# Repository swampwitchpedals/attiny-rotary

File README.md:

# ATTiny Rotary

This is an open-source project designed to fill a need that
has been missed in small-scale pedal building: a reliable rotary.

## Why
The traditional rotary is huge, has a ton of solder points, 
has a limited lifespan, and is generally awkward on a PCB. This solution
aims to use the Vimex position sensor, which has the same footprint
as a standard 16mm potentiometer, in conjunction with an ATtiny and
some CD4051 switches to make an easy [1-N]p8t rotary module.

## What
PCBs are all available in the `kicad/` directory. Arduino sketches for each
sized position-sensor (5, 6 and 8) are available in the `arduino/` directory.

*Module* refers to the PCB (`kicad/rotary-multiplexor/`) and to the completed unit with parts soldered.
*Programming Shield* refers to the Atmega shield provided in the `kicad/arduino-mega-progamming-shield/` directory.

## How
1. Solder your Attiny to the Module. 
2. Solder the power regulator and filter caps onto the Module.
3. Plug the Module in the Programming Shield.
4. Program the Atmega with the ArduinoAsISP sketch.
5. Select the Attiny board of your choice, clock speed, and set the programmer to ArduinoAsISP (NOT Arduino As ISP).
6. Select your position-sensor-size sketch and program the Attiny using the "Upload via programmer" option.
7. Attach Module to your effect PCB, with the mux-select lines (pins 7, 6 and 5) tied to each 4051 you wish to control, and the position sensor pins 3 and 2 wired to pins 2 and 3 of the Module.

## License
**DISCLAIMER**
All files and documents are provided as-is. I cannot afford to support 
questions on PCB manufacturing, assembly, or Arduino programming. There
are lots of resources out there to answer these questions.

Copyright 2023 Swamp Witch Pedals

Permission is hereby granted, free of charge, to any person obtaining a copy of this software and associated documentation files (the “Software”), to deal in the Software without restriction, including without limitation the rights to use, copy, modify, merge, publish, distribute, sublicense, and/or sell copies of the Software, and to permit persons to whom the Software is furnished to do so, subject to the following conditions:

The above copyright notice and this permission notice shall be included in all copies or substantial portions of the Software.

THE SOFTWARE IS PROVIDED “AS IS”, WITHOUT WARRANTY OF ANY KIND, EXPRESS OR IMPLIED, INCLUDING BUT NOT LIMITED TO THE WARRANTIES OF MERCHANTABILITY, FITNESS FOR A PARTICULAR PURPOSE AND NONINFRINGEMENT. IN NO EVENT SHALL THE AUTHORS OR COPYRIGHT HOLDERS BE LIABLE FOR ANY CLAIM, DAMAGES OR OTHER LIABILITY, WHETHER IN AN ACTION OF CONTRACT, TORT OR OTHERWISE, ARISING FROM, OUT OF OR IN CONNECTION WITH THE SOFTWARE OR THE USE OR OTHER DEALINGS IN THE SOFTWARE

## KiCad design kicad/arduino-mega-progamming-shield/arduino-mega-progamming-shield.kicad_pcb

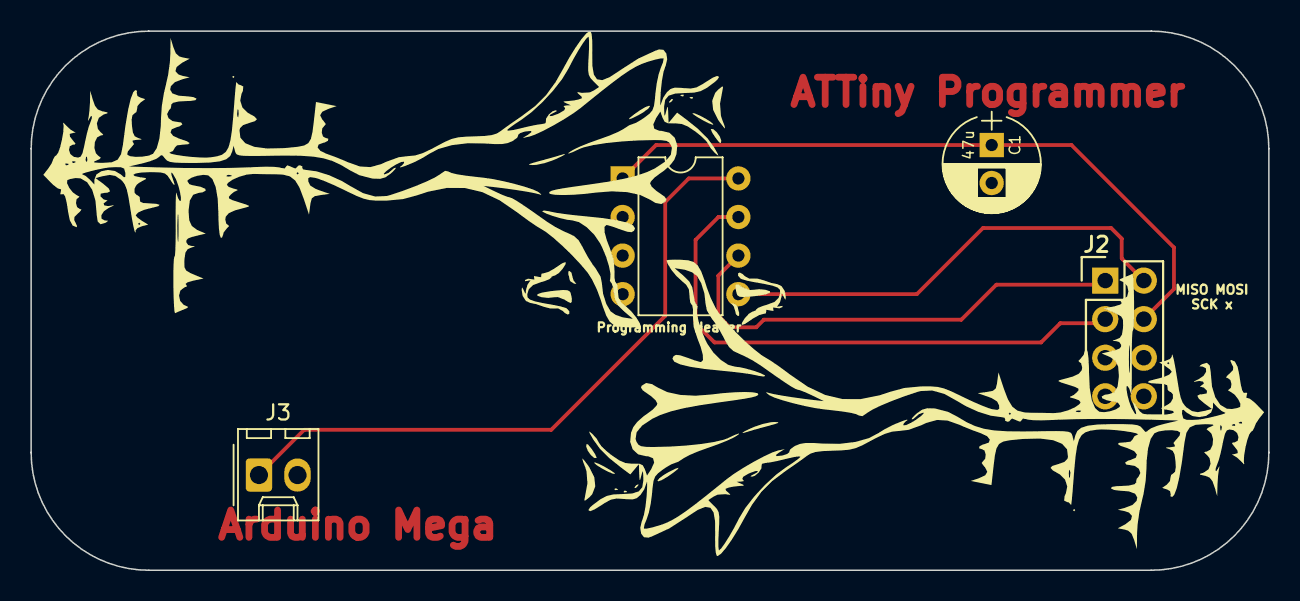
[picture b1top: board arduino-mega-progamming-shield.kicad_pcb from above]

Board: 2 copper layers, 81.5 x 35.5 mm, 4 parts (0 on the bottom side), 6 nets.

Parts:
C1: 47u; Cap_Electrolytic_TH
J1: Programming Header; DIP_8pin_TH
J2: MISO MOSI SCK x; Pin_Header_Straight_2x04
J3: Conn_01x02; Molex_KK-254_AE-6410-02A_1x02_P2.54mm_Vertical

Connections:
/+5V: J1.8, J3.1
/MISO: J1.6, J2.1
/MOSI: J1.5, J2.2
/Reset: C1.1 (+), J1.1, J2.4
/SCK: J1.7, J2.3
GND: C1.2 (-), J1.4, J3.2

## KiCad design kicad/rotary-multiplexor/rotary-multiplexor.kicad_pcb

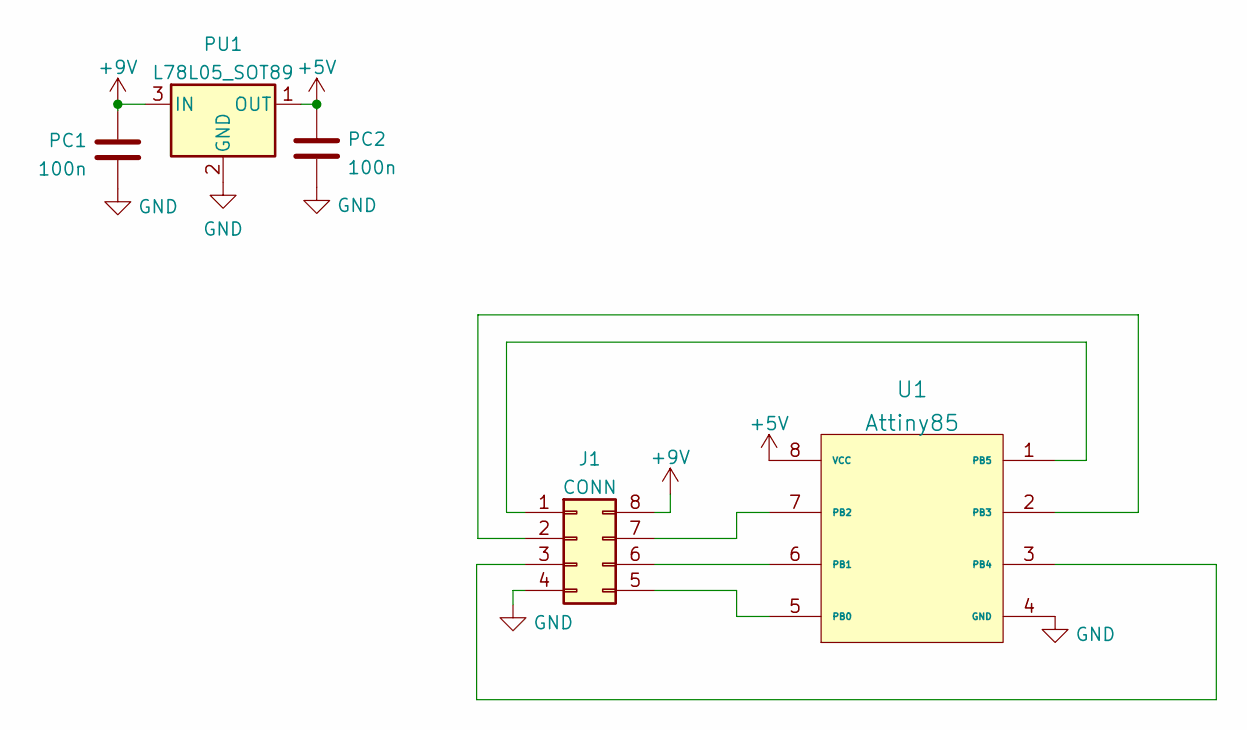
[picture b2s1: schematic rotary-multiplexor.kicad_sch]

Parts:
J1: CONN; DIP_8pin_TH
PC1, PC2: 100n; C_0805
PU1: L78L05_SOT89; SOT-89-3
U1: Attiny85; SOIC-8_3.9x4.9mm_P1.27mm

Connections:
+5V: PC2.1, PU1.1 (OUT), U1.8 (VCC)
+9V: J1.8, PC1.2, PU1.3 (IN)
GND: J1.4, PC1.1, PC2.2, PU1.2 (GND), U1.4 (GND)
unnamed: J1.6, U1.6 (PB1)
unnamed: J1.7, U1.7 (PB2)
unnamed: J1.1, U1.1 (PB5)
unnamed: J1.2, U1.2 (PB3)
unnamed: J1.3, U1.3 (PB4)
unnamed: J1.5, U1.5 (PB0)

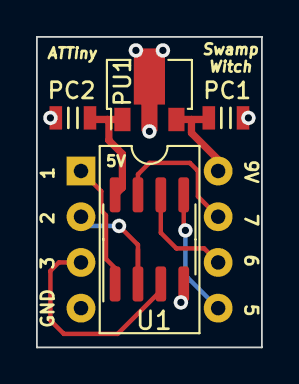
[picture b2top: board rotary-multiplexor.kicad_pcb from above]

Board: 2 copper layers, 12.5 x 17.2 mm, 5 parts (0 on the bottom side), 9 nets.

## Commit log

2023-07-18 Initial Commit
    Adds 5 and 8 position rotary code
    Adds kicad board for programmer
    Adds kicad board for Attiny
2023-07-20 Update code for arduino sketches
2023-07-20 Add Atmega programmer sketch for Attiny
2023-07-23 Update rotary code for Attiny.
    Use full-scale voltages
2023-07-23 Add MIT license
